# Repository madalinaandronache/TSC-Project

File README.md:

# OpenBook - E-book Reader Open-Source

Student: Andronache Madalina-Georgiana
Grupa: 332CC

Urmatorul fisier contine informatii despre rezolvarea cerintelor
propuse.

Cuprins:

0. Descrierea cerintelor
1. Diagrama bloc
2. BOM - Bill of Materials
3. Functionalitatea hardware
4. Pini utilizați pe ESP32-C6 și justificare
5. Observatii

## 0. Descrierea cerintelor

OpenBook este un e-book reader open-source, conceput să fie ieftin, compact și ușor de produs. 
Acest proiect este realizat în cadrul unui start-up educațional, iar scopul este dezvoltarea unui 
dispozitiv complet funcțional, pornind de la specificațiile sistemului până la fișierele de fabricație.

## 1. Diagrama bloc

## 2. BOM - Bill of Materials

| Device | Value | Check_Price | Datasheet |
|--------|-------|-------------|-----------|
| ADAFRUIT_LEDCHIP-LED0603 | - | [Link](https://www.snapeda.com/parts/KP-1608SURCK/Kingbright/view-part/?ref=search&t=LED%200603) | [Link](https://www.snapeda.com/parts/KP-1608SURCK/Kingbright/datasheet/) |
| SJ | - | [Link](https://grabcad.com/library/solder-jumpers-1) | - |
| EAGLE-LTSPICE_C | 0.1uF/50V | [Link](https://componentsearchengine.com/part-view/CC0402MRX5R5BB106/YAGEO) | [Link](https://componentsearchengine.com/Datasheets/2/CC0402MRX5R5BB106.pdf) |
| ESP32_WROVER_EAGLE-LTSPICE_R | 0.47 | [Link](https://componentsearchengine.com/part-view/R0402%201%25%20100%20K%20(RC0402FR-07100KL)/YAGEO) | [Link](https://www.yageo.com/upload/media/product/products/datasheet/rchip/PYu-RC_Group_51_RoHS_L_12.pdf) |
| ESP32_WROVER_EAGLE-LTSPICE_R | 100K | [Link](https://componentsearchengine.com/part-view/R0402%201%25%20100%20K%20(RC0402FR-07100KL)/YAGEO) | [Link](https://www.yageo.com/upload/media/product/products/datasheet/rchip/PYu-RC_Group_51_RoHS_L_12.pdf) |
| EAGLE-LTSPICE_C | 100nF | [Link](https://componentsearchengine.com/part-view/CC0402MRX5R5BB106/YAGEO) | [Link](https://componentsearchengine.com/Datasheets/2/CC0402MRX5R5BB106.pdf) |
| RCL_CPOL-EUCT3528 | 100uF TANT | [Link](https://www.snapeda.com/parts/TAJB475K025RNJ/AVX/view-part/?ref=dk&t=capacitor%203528&con_ref=None) | [Link](https://s3.amazonaws.com/snapeda/datasheet/TAJB475K025RNJ_AVX.pdf) |
| ESP32_WROVER_EAGLE-LTSPICE_R | 10K | [Link](https://componentsearchengine.com/part-view/R0402%201%25%20100%20K%20(RC0402FR-07100KL)/YAGEO) | [Link](https://www.yageo.com/upload/media/product/products/datasheet/rchip/PYu-RC_Group_51_RoHS_L_12.pdf) |
| EAGLE-LTSPICE_C | 10uF | [Link](https://componentsearchengine.com/part-view/CC0402MRX5R5BB106/YAGEO) | [Link](https://componentsearchengine.com/Datasheets/2/CC0402MRX5R5BB106.pdf) |
| 112A-TAAR-R03_ATTEND | 112A-TAAR-R03_ATTEND | [Link](https://store.comet.srl.ro/Catalogue/Product/43497/) | [Link](https://store.comet.bg/download-file.php?id=8824) |
| ESP32_WROVER_EAGLE-LTSPICE_R | 15 | [Link](https://componentsearchengine.com/part-view/R0402%201%25%20100%20K%20(RC0402FR-07100KL)/YAGEO) | [Link](https://www.yageo.com/upload/media/product/products/datasheet/rchip/PYu-RC_Group_51_RoHS_L_12.pdf) |
| EAGLE-LTSPICE_C | 1uF | [Link](https://componentsearchengine.com/part-view/CC0402MRX5R5BB106/YAGEO) | [Link](https://componentsearchengine.com/Datasheets/2/CC0402MRX5R5BB106.pdf) |
| EAGLE-LTSPICE_C | 1uF/50V | [Link](https://componentsearchengine.com/part-view/CC0402MRX5R5BB106/YAGEO) | [Link](https://componentsearchengine.com/Datasheets/2/CC0402MRX5R5BB106.pdf) |
| ESP32_WROVER_EAGLE-LTSPICE_R | 2.2 | [Link](https://componentsearchengine.com/part-view/R0402%201%25%20100%20K%20(RC0402FR-07100KL)/YAGEO) | [Link](https://www.yageo.com/upload/media/product/products/datasheet/rchip/PYu-RC_Group_51_RoHS_L_12.pdf) |
| ESP32_WROVER_EAGLE-LTSPICE_R | 200 | [Link](https://componentsearchengine.com/part-view/R0402%201%25%20100%20K%20(RC0402FR-07100KL)/YAGEO) | [Link](https://www.yageo.com/upload/media/product/products/datasheet/rchip/PYu-RC_Group_51_RoHS_L_12.pdf) |
| ESP32_WROVER_SPARKFUN-DISCRETESEMI_MOSFET_PCH-DMG2305UX-7 | 20V/4.2A/52m?/1.4W | [Link](https://componentsearchengine.com/part-view/DMG2305UX-7/Diodes%20Incorporated) | [Link](https://www.diodes.com//assets/Datasheets/DMG2305UX.pdf) |
| ESP32_WROVER_EAGLE-LTSPICE_R | 2K | [Link](https://componentsearchengine.com/part-view/R0402%201%25%20100%20K%20(RC0402FR-07100KL)/YAGEO) | [Link](https://www.yageo.com/upload/media/product/products/datasheet/rchip/PYu-RC_Group_51_RoHS_L_12.pdf) |
| EAGLE-LTSPICE_C | 4.7uF | [Link](https://componentsearchengine.com/part-view/CC0402MRX5R5BB106/YAGEO) | [Link](https://componentsearchengine.com/Datasheets/2/CC0402MRX5R5BB106.pdf) |
| EAGLE-LTSPICE_C | 4.7uF/25V | [Link](https://componentsearchengine.com/part-view/CC0402MRX5R5BB106/YAGEO) | [Link](https://componentsearchengine.com/Datasheets/2/CC0402MRX5R5BB106.pdf) |
| ESP32_WROVER_EAGLE-LTSPICE_R | 5k1 | [Link](https://componentsearchengine.com/part-view/R0402%201%25%20100%20K%20(RC0402FR-07100KL)/YAGEO) | [Link](https://www.yageo.com/upload/media/product/products/datasheet/rchip/PYu-RC_Group_51_RoHS_L_12.pdf) |
| 744043680IND_4828-WE-TPC_WRE | 68uH | [Link](https://ro.mouser.com/ProductDetail/Wurth-Elektronik/744043680?qs=PGXP4M47uW6VkZq%252BkzjrHA%3D%3D&_gl=1*5xajdn*_ga*MzY2ODgyMjE4LjE3NDM2NzQxODk.*_ga_15W4STQT4T*MTc0Mzg3MzkxMy40LjAuMTc0Mzg3MzkxNi41Ny4wLjA.) | [Link](https://www.we-online.com/components/products/datasheet/744043680.pdf) |
| BD5229G-TR | BD5229G-TR | [Link](https://componentsearchengine.com/part-view/BD5229G-TR/ROHM%20Semiconductor) | [Link](https://datasheet.datasheetarchive.com/originals/distributors/Datasheets_SAMA/f2b9741ef86007909f138d561a359946.pdf) |
| ESP32_WROVER_BME680_BME680 | BME688 | [Link](https://www.snapeda.com/parts/BME680/Bosch/view-part/?welcome=home) | [Link](https://www.snapeda.com/parts/BME680/Bosch%20Sensortec/datasheet/) |
| BUTTON_CUSYOMV1V2 | BUTTON_CUSYOMV1V2 | [Link](https://industry.panasonic.com/global/en/products/control/switch/light-touch/number/evqpuj02k) | [Link](https://industry.panasonic.com/global/en/downloads?tab=catalog&small_g_cd=203&part_no=EVQPUJ02K) |
| CPH3225A | CPH3225A | [Link](https://www.snapeda.com/parts/CPH3225A/Seiko+Instruments/view-part/?ref=eda) | [Link](https://www.snapeda.com/parts/CPH3225A/Seiko+Instruments/view-part/?ref=eda ) |
| DS3231SN# | DS3231SN# | [Link](https://www.snapeda.com/parts/DS3231SN%23/Analog+Devices/view-part/?ref=eda) | [Link](https://www.snapeda.com/parts/DS3231SN%23/Analog+Devices/view-part/?ref=eda) |
| ESP32-C6-WROOM-1-N8 | ESP32-C6-WROOM-1-N8 | [Link](https://www.snapeda.com/parts/ESP32-C6-WROOM-1-N8/Espressif+Systems/view-part/?ref=eda) | [Link](https://www.snapeda.com/parts/ESP32-C6-WROOM-1-N8/Espressif+Systems/view-part/?ref=eda) |
| ESP32C6_VARISTORCN1812 | ESP32C6_VARISTORCN1812 | [Link](https://www.mouser.co.uk/ProductDetail/EPCOS-TDK/B72520T0350K062?qs=dEfas%2FXlABIszF52uu7vrg%3D%3D) | [Link](https://www.tdk-electronics.tdk.com/inf/75/db/CTVS_14/Surge_protection_series.pdf) |
| ESP32_WROVER_SPARKFUN-IC-POWER_MCP73831 | ESP32_WROVER_SPARKFUN-IC-POWER_MCP73831 | [Link](https://ro.mouser.com/ProductDetail/Microchip-Technology/MCP73831T-2ACI-OT?qs=yUQqVecv4qvbBQBGbHx0Mw%3D%3D) | [Link](https://ro.mouser.com/datasheet/2/268/MCP73831_Family_Data_Sheet_DS20001984H-3441711.pdf) |
| FH34SRJ-24S-0.5SH_99_ | FH34SRJ-24S-0.5SH_99_ | [Link](https://componentsearchengine.com/part-view/FH34SRJ-24S-0.5SH(99)/Hirose) | [Link](https://www.hirose.com/en/product/document?clcode=CL0580-1255-6-99&productname=FH34SRJ-24S-0.5SH(99)&series=FH34SRJ&documenttype=2DDrawing&lang=en&documentid=0000990903) |
| MAX17048G+T10 | MAX17048G+T10 | [Link](https://www.snapeda.com/parts/MAX17048G+T10/Analog+Devices/view-part/?ref=eda) | [Link](https://www.snapeda.com/parts/MAX17048G+T10/Analog+Devices/view-part/?ref=eda) |
| MBR0530. | MBR0530. | [Link](https://www.snapeda.com/parts/MBR0530/Onsemi/view-part/?ref=eda) | [Link](https://www.snapeda.com/parts/MBR0530/ON%20Semiconductor/datasheet/) |
| PGB1010603MR. | PGB1010603MR. | [Link](https://www.snapeda.com/parts/PGB1010603MR/Littelfuse/view-part/?ref=eda) | [Link](https://www.snapeda.com/parts/PGB1010603MR/Littelfuse%20Inc./datasheet/) |
| QWIIC_CONNECTORJS-1MM | QWIIC_RIGHT_ANGLE | [Link](https://www.digikey.lt/en/models/926710 ) | [Link](https://www.digikey.lt/en/models/926710) |
| SAMACSYS_PARTS_USB4110-GF-A | SAMACSYS_PARTS_USB4110-GF-A | [Link](https://componentsearchengine.com/part-view/USB4110-GF-A/GCT%20(GLOBAL%20CONNECTOR%20TECHNOLOGY)) | [Link](https://gct.co/files/drawings/usb4110.pdf) |
| ESP32_WROVER_AVX---SD0805S020S1R0_AVX_SD0805S020S1R0_0_0AVX_SD0805S020S1R0_0_0 | SD0805S020S1R0 | [Link](https://ro.mouser.com/ProductDetail/KYOCERA-AVX/SD0805S020S1R0?qs=jCA%252BPfw4LHbpkAoSnwrdjw%3D%3D) | [Link](http://datasheets.avx.com/schottky.pdf) |
| SI1308EDL-T1-GE3 | SI1308EDL-T1-GE3 | [Link](https://www.snapeda.com/parts/SI1308EDL-T1-GE3/Vishay+Siliconix/view-part/?ref=eda) | [Link](https://www.snapeda.com/parts/SI1308EDL-T1-GE3/Vishay+Siliconix/view-part/?ref=eda) |
| TPV1 | TPV1 | Custom made | - |
| USBLC6-2SC6Y | USBLC6-2SC6Y | [Link](https://www.snapeda.com/parts/USBLC6-2SC6Y/STMicroelectronics/view-part/?ref=eda) | [Link](https://www.snapeda.com/parts/USBLC6-2SC6Y/STMicroelectronics/view-part/?ref=eda) |
| W25Q512JVEIQ | W25Q512JVEIQ | [Link](https://www.snapeda.com/parts/W25Q512JVEIQ/Winbond+Electronics/view-part/?ref=eda) | [Link](https://www.snapeda.com/parts/W25Q512JVEIQ/Winbond+Electronics/view-part/?ref=eda) |
| XC6220A331MR-G | XC6220A331MR-G | [Link](https://componentsearchengine.com/part-view/XC6220A331MR-G/Torex) | [Link](https://product.torexsemi.com/system/files/series/xc6220.pdf) |

## 3. Functionalitatea hardware

Prezentam in detaliu functionalitatea hardware a device-ului:

| Nr. | Componentă                              |
|-----|------------------------------------------|
| 1   | Microcontroller – ESP32-C6-WROOM-1       |
| 2   | Afișaj E-Ink – Waveshare WSH-13187, 7.5” |
| 3   | Senzor Mediu – Bosch BME688              |
| 4   | Baterie și Management Energie            |
| 5   | Butoane – 3x Tactile Switch              |
| 6   | Port USB-C                               |
| 7   | Conector Qwiic / STEMMA QT (I²C)         |
| 8   | Slot MicroSD – Attend 112A-TAAR-R03      |
| 9   | RTC – DS3231                             |

### 3.1. Microcontroller – ESP32-C6-WROOM-1
- **Procesor:** 32-bit RISC-V @ 160MHz
- **Memorie:** 512KB SRAM + 8MB flash extern (W25Q512JVEIQ)
- **Conectivitate:** Wi-Fi 6 (802.11ax), Bluetooth 5 LE, USB 2.0 Full-Speed
- **Periferice:** SPI, I²C, UART, GPIO multiple
- **Consum:** <50µA în deep sleep, moduri low-power disponibile
- **Securitate:** Secure boot, criptare flash, criptografie hardware

### 3.2. Afișaj E-Ink – Waveshare WSH-13187, 7.5”
- **Rezoluție:** 800x480, monocrom
- **Interfață:** SPI (4-wire) + CS, DC, RST, BUSY
- **Consum:** 15–25mA în timpul refresh-ului, zero static
- **Motivație:** Consum aproape zero în mod static, ideal pentru e-readere

### 3.3. Senzor Mediu – Bosch BME688
- **Parametri:** Temperatură, Umiditate, Presiune, Calitate Aer (eCO2, TVOC)
- **Precizie:** ±1°C, ±3%, ±1 hPa
- **Interfață:** I²C (400kHz)
- **Consum:** 2.1µA standby, 3.6mA peak
- **Motivație:** Multi-senzor compact, ideal pentru feedback ambiental

### 3.4. Baterie și Management Energie
- **Tip:** Li-Po 3.7V, 2500mAh
- **Fuel Gauge:** MAX17048 (I²C)
- **Charging IC:** MCP73831 – încărcare 5V/1A prin USB-C
- **LDO:** 3.3V stabil pentru întreaga placă
- **Consum Total:**  
  - Activ: 100–150mA  
  - Deep Sleep: <50µA

### 3.5. Butoane – 3x Tactile Switch
- **Model:** Panasonic EVQ-Q2A03W
- **Conectare:** GPIO + debounce hardware (RC)
- **Funcții:** Navigare meniu, pagină înainte/înapoi, confirmare

### 3.6. Port USB-C
- **Rol:** Încărcare + transfer date (USB 2.0)
- **Protecții:** ESD + terminare corectă
- **Capabilități:** OTA updates prin Wi-Fi / firmware update prin USB

### 3.7. Conector Qwiic / STEMMA QT (I²C)
- **Pini:** VCC, GND, SDA, SCL
- **Utilitate:** Extensibilitate rapidă prin senzori/modul I²C

### 3.8. Slot MicroSD – Attend 112A-TAAR-R03
- **Funcție:** Stocare externă (ebooks, logs, firmware)
- **Interfață:** SPI

### 3.9. RTC – DS3231
- **Precizie:** ±2ppm
- **Interfață:** I²C
- **Backup:** Supercapacitor

---

### Comunicații & Interfețe

| Tip       | Componente                                          |
|-----------|-----------------------------------------------------|
| **SPI**   | E-Paper, Flash extern, SD Card (în mod SPI)         |
| **I²C**   | BME688, MAX17048, DS3231, Qwiic/Stemma              |
| **USB**   | Încărcare și transfer date prin USB-C               |
| **GPIO**  | Butoane, semnale control afișaj, charging enable    |

---

### Consum de Energie (Estimativ)

| Modul             | Consum Tipic       |
|------------------|--------------------|
| ESP32-C6 activ    | 80–100mA           |
| E-Paper refresh   | 15–25mA            |
| BME688 activ      | 3.6mA              |
| MAX17048          | ~50µA              |
| DS3231 (RTC)      | 3.5mA / 1µA backup |
| Deep Sleep Total  | <50–100µA          |

---

### Dimensiuni & Alte Detalii
- **Dimensiuni:** 175 x 114 x 10 mm
- **Greutate:** 250g
- **Material carcasă:** ABS sau policarbonat, design ergonomic
- **Display:** Montat cu decupaj integrat
- **Producție:** PCB 2-layer, ENIG, carcasă prin injecție

---

## 4. Pini utilizați pe ESP32-C6 și justificare

| Pin ESP32-C6 | Componentă / Semnal                | De ce?                                                                 |
|--------------|-------------------------------------|------------------------------------------------------------------------|
| GPIO1        | I²C SDA (BME688, MAX17048, DS3231, Qwiic) | Linie partajată I²C – economisește pini și permite extinderea facilă |
| GPIO2        | I²C SCL (BME688, MAX17048, DS3231, Qwiic) | Clock I²C pentru toți senzorii și extensii Qwiic                     |
| GPIO5        | SPI MISO (E-Paper, Flash extern)    | Linie comună de intrare date în SPI                                   |
| GPIO6        | SPI MOSI (E-Paper, Flash extern)    | Linie de ieșire date către e-paper și flash                           |
| GPIO7        | SPI CLK                             | Semnal de clock pentru magistrala SPI                                 |
| GPIO8        | E-Paper CS                          | Selectează afișajul pe magistrala SPI                                 |
| GPIO9        | E-Paper DC (Data/Command)           | Comută între comandă și date către e-paper                            |
| GPIO10       | E-Paper RST                         | Reset hardware e-paper                                                |
| GPIO11       | E-Paper BUSY                        | Pin de stare (ocupat/liber) de la display                             |
| GPIO12       | Button #1                           | Intrare digitală pentru navigare pagină înainte                      |
| GPIO13       | Button #2                           | Intrare digitală pentru navigare pagină înapoi                       |
| GPIO14       | Button #3                           | Intrare digitală pentru selectare/opțiune                            |
| GPIO15       | MAX17048 ALERT (opțional)           | Pin de alertă nivel scăzut baterie                                    |
| GPIO16       | USB D+ (intern la USB PHY)          | Linie USB 2.0 (fixă pe ESP32-C6)                                      |
| GPIO17       | USB D- (intern la USB PHY)          | Linie USB 2.0 (fixă pe ESP32-C6)                                      |
| GPIO18       | LED Status (opțional)               | Indicator pentru activitate Wi-Fi, charging, notificări               |
| GPIO19       | SD Card CS                          | Selectare chip pentru card microSD (SPI)                              |
| GPIO20       | SD Card MISO                        | Citire date de pe card microSD                                        |
| GPIO21       | SD Card MOSI                        | Scriere date pe card microSD                                          |
| GPIO4        | SD Card CLK                         | Semnal de clock pentru card microSD (SPI)                             |

## 5. Observatii

Fun to make, dar mult prea solicitant. Realizat in aproximativ 60 h.

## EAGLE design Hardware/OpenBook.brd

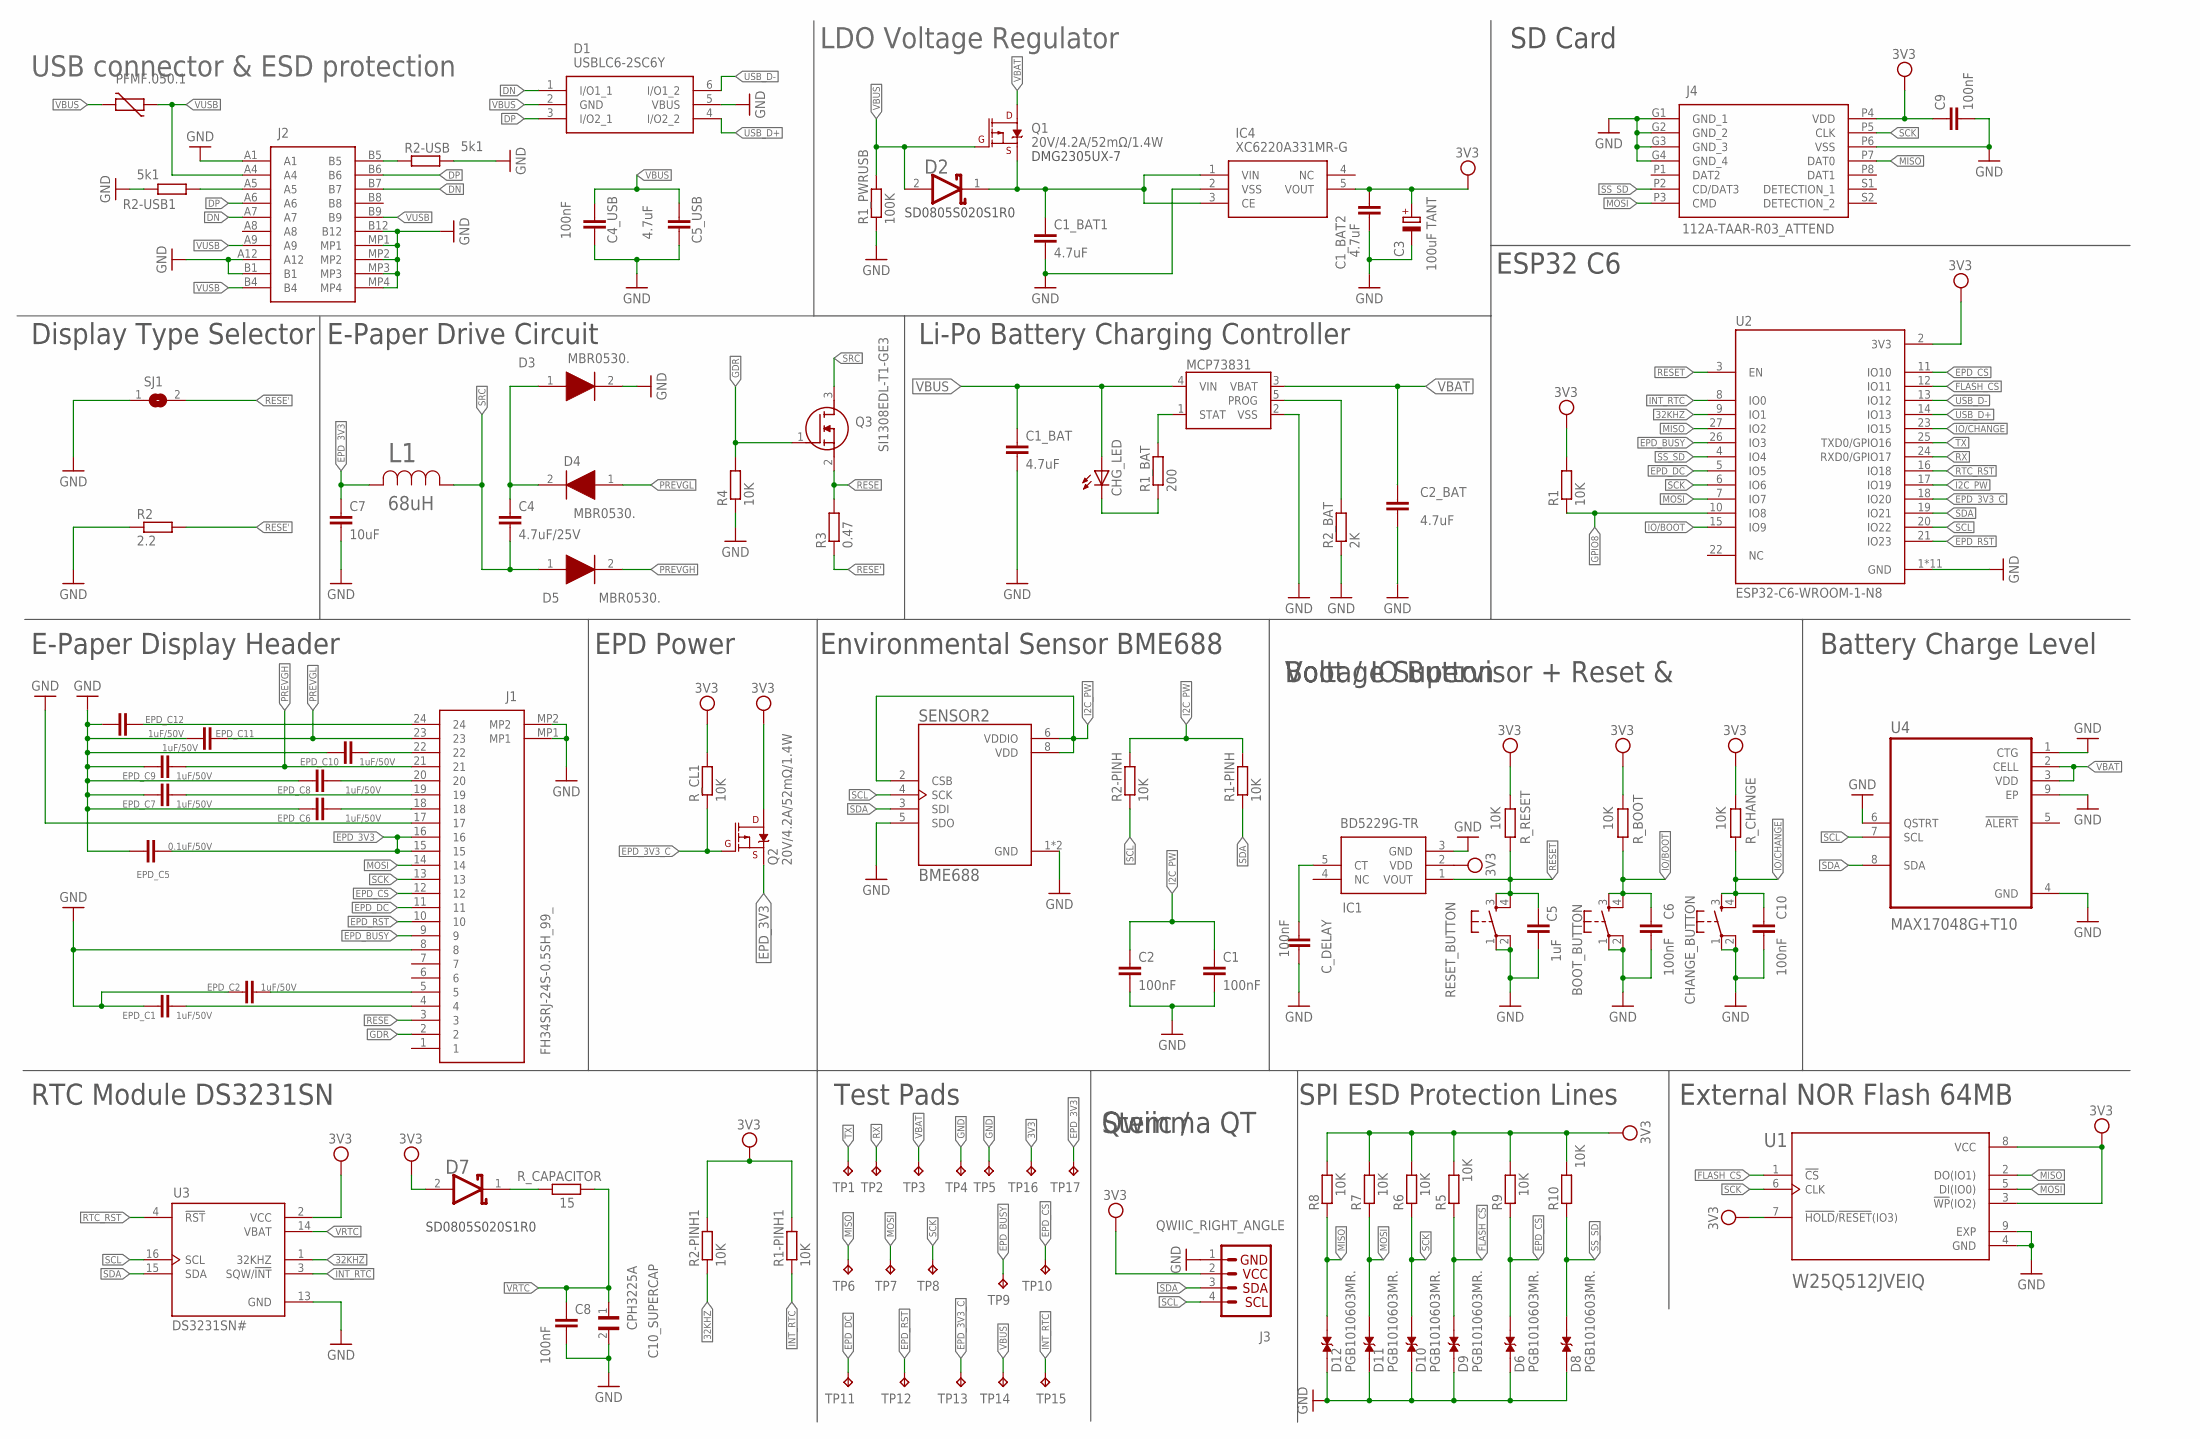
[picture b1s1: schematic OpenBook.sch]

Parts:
BOOT_BUTTON: BUTTON_CUSYOMV1V2; MYBUTTON
C1, C2, C4_USB, C6, C8, C9, C10: 100nF; EAGLE-LTSPICE_C0402
C1_BAT, C1_BAT1, C1_BAT2, C2_BAT, C5_USB: 4.7uF; EAGLE-LTSPICE_C0402
C3: 100uF TANT; RCL_CT3528
C4: 4.7uF/25V; EAGLE-LTSPICE_C0402
C5: 1uF; EAGLE-LTSPICE_C0402
C7: 10uF; EAGLE-LTSPICE_C0402
C10_SUPERCAP: CPH3225A; CAPCP3225X100N
CHANGE_BUTTON: BUTTON_CUSYOMV1V2; MYBUTTON
CHG_LED: ADAFRUIT_LEDCHIP-LED0603; ADAFRUIT_CHIP-LED0603
C_DELAY: 100nF; EAGLE-LTSPICE_C0402
D1: USBLC6-2SC6Y; SOT95P280X145-6N
D2, D7: SD0805S020S1R0; ESP32_WROVER_AVX---SD0805S020S1R0_AVX_SD0805S020S1R0_0
D3, D4, D5: MBR0530.; SOD3716X135N
D6, D8, D9, D10, D11, D12: PGB1010603MR.; DIOC1608X36N
EPD_C1, EPD_C2, EPD_C6, EPD_C7, EPD_C8, EPD_C9, EPD_C10, EPD_C11, EPD_C12: 1uF/50V; EAGLE-LTSPICE_C0402
EPD_C5: 0.1uF/50V; EAGLE-LTSPICE_C0402
IC1: BD5229G-TR; SOT95P280X125-5N
IC4: XC6220A331MR-G; SOT95P280X120-5N
J1: FH34SRJ-24S-0.5SH_99_; FH34SRJ24S05SH99
J2: SAMACSYS_PARTS_USB4110-GF-A; SAMACSYS_PARTS_USB4110GFA
J3: QWIIC_RIGHT_ANGLE; JST04_1MM_RA
J4: 112A-TAAR-R03_ATTEND; 112ATAARR03ATTEND
L1: 68uH; IND_4828-WE-TPC_WRE
MCP73831: ESP32_WROVER_SPARKFUN-IC-POWER_MCP73831; ESP32_WROVER_SPARKFUN-IC-POWER_SOT23-5
PFMF.050.1: ESP32C6_VARISTORCN1812; ESP32C6_VARISTOR_CT/CN1812
Q1, Q2: 20V/4.2A/52mΩ/1.4W; ESP32_WROVER_SPARKFUN-DISCRETESEMI_SOT23-3
Q3: SI1308EDL-T1-GE3; SOT65P210X110-3N
R1, R1-PINH, R1-PINH1, R2-PINH, R2-PINH1, R4, R5, R6, R7, R8, R9, R10: 10K; ESP32_WROVER_EAGLE-LTSPICE_R0402
R1_BAT: 200; ESP32_WROVER_EAGLE-LTSPICE_R0402
R1_PWRUSB: 100K; ESP32_WROVER_EAGLE-LTSPICE_R0402
R2: 2.2; ESP32_WROVER_EAGLE-LTSPICE_R0402
R2-USB, R2-USB1: 5k1; ESP32_WROVER_EAGLE-LTSPICE_R0402
R2_BAT: 2K; ESP32_WROVER_EAGLE-LTSPICE_R0402
R3: 0.47; ESP32_WROVER_EAGLE-LTSPICE_R0402
RESET_BUTTON: BUTTON_CUSYOMV1V2; MYBUTTON
R_BOOT: 10K; ESP32_WROVER_EAGLE-LTSPICE_R0402
R_CAPACITOR: 15; ESP32_WROVER_EAGLE-LTSPICE_R0402
R_CHANGE: 10K; ESP32_WROVER_EAGLE-LTSPICE_R0402
R_CL1: 10K; ESP32_WROVER_EAGLE-LTSPICE_R0402
R_RESET: 10K; ESP32_WROVER_EAGLE-LTSPICE_R0402
SENSOR2: BME688; ESP32_WROVER_BME680_PSON80P300X300X100-8N
SJ1: SJ
TP1, TP2, TP3, TP4, TP5, TP6, TP7, TP8, TP9, TP10, TP11, TP12, TP13, TP14, TP15, TP16, TP17: TPV1; TP20R
U1: W25Q512JVEIQ; SON127P600X800X80-9N
U2: ESP32-C6-WROOM-1-N8; XCVR_ESP32-C6-WROOM-1-N8
U3: DS3231SN#; SOIC127P1032X265-16N
U4: MAX17048G+T10; SON50P200X200X80-9N

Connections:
3V3: C1_BAT2.1, C3.+, C9.1, D7.2 (ANODE), IC1.2 (VDD), IC4.5 (VOUT), J3.2, J4.P4 (VDD), Q2.3 (D), R1.2, R1-PINH1.2, R2-PINH1.2, R5.2, R6.2, R7.2, R8.2, R9.2, R10.2, R_BOOT.2, R_CHANGE.2, R_CL1.2, R_RESET.2, TP16.TP, U1.3 (!WP!(IO2)), U1.7 (!HOLD!/!RESET!(IO3)), U1.8 (VCC), U2.2 (3V3), U3.2 (VCC)
32KHZ: R2-PINH1.1, U2.9 (IO1), U3.1 (32KHZ)
DN: D1.1 (I/O1_1), J2.A7, J2.B7
DP: D1.3 (I/O2_1), J2.A6, J2.B6
EPD_3V3: C7.1, EPD_C5.2, J1.15, J1.16, L1.2, Q2.2 (S), TP17.TP
EPD_3V3_C: Q2.1 (G), R_CL1.1, TP13.TP, U2.18 (IO20)
EPD_BUSY: J1.9, TP9.TP, U2.26 (IO3)
EPD_CS: D6.2, J1.12, R9.1, TP10.TP, U2.11 (IO10)
EPD_DC: J1.11, TP11.TP, U2.5 (IO5)
EPD_RST: J1.10, TP12.TP, U2.21 (IO23)
FLASH_CS: D9.2, R5.1, U1.1 (!CS), U2.12 (IO11)
GDR: J1.2, Q3.1 (G), R4.2
GND: BOOT_BUTTON.1, BOOT_BUTTON.2, C1.2, C1_BAT.2, C1_BAT1.2, C1_BAT2.2, C2.2, C2_BAT.2, C3.-, C4_USB.2, C5.2, C5_USB.2, C6.2, C7.2, C8.2, C9.2, C10.2, C10_SUPERCAP.2, CHANGE_BUTTON.1, CHANGE_BUTTON.2, C_DELAY.2, D1.5 (VBUS), D3.2 (K), D6.1, D8.1, D9.1, D10.1, D11.1, D12.1, EPD_C1.1, EPD_C2.1, EPD_C5.1, EPD_C6.1, EPD_C7.1, EPD_C8.1, EPD_C9.1, EPD_C10.1, EPD_C11.1, EPD_C12.1, IC1.3 (GND), IC4.2 (VSS), J1.8, J1.17, J1.MP1, J1.MP2, J2.A1, J2.A12, J2.B1, J2.B12, J2.MP1, J2.MP2, J2.MP3, J2.MP4, J3.1, J4.G1 (GND_1), J4.G2 (GND_2), J4.G3 (GND_3), J4.G4 (GND_4), J4.P6 (VSS), MCP73831.2 (VSS), R1_PWRUSB.1, R2.1, R2-USB.2, R2-USB1.1, R2_BAT.1, R4.1, RESET_BUTTON.1, RESET_BUTTON.2, SENSOR2.1 (GND), SENSOR2.5 (SDO), SENSOR2.7 (GND), SJ1.1, TP4.TP, TP5.TP, U1.4 (GND), U1.9 (EXP), U2.1 (GND), U2.28 (GND), U2.29_1 (GND), U2.29_2 (GND), U2.29_3 (GND), U2.29_4 (GND), U2.29_5 (GND), U2.29_6 (GND), U2.29_7 (GND), U2.29_8 (GND), U2.29_9 (GND), U3.13 (GND), U4.1 (CTG), U4.4 (GND), U4.6 (QSTRT), U4.9 (EP)
GPIO8: R1.1, U2.10 (IO8)
I2C_PW: C1.1, C2.1, R1-PINH.2, R2-PINH.2, SENSOR2.2 (CSB), SENSOR2.6 (VDDIO), SENSOR2.8 (VDD), U2.17 (IO19)
INT_RTC: R1-PINH1.1, TP15.TP, U2.8 (IO0), U3.3 (SQW/!INT)
IO/BOOT: BOOT_BUTTON.3, BOOT_BUTTON.4, C6.1, R_BOOT.1, U2.15 (IO9)
IO/CHANGE: C10.1, CHANGE_BUTTON.3, CHANGE_BUTTON.4, R_CHANGE.1, U2.23 (IO15)
MISO: D12.2, J4.P7 (DAT0), R8.1, TP6.TP, U1.2 (DO(IO1)), U2.27 (IO2)
MOSI: D11.2, J1.14, J4.P3 (CMD), R7.1, TP7.TP, U1.5 (DI(IO0)), U2.7 (IO7)
unnamed: D7.1 (CATHODE), R_CAPACITOR.1
unnamed: J2.A5, R2-USB1.2
unnamed: J2.B5, R2-USB.1
unnamed: C4.1, D3.1 (A), D4.2 (K)
unnamed: C1_BAT1.1, D2.1 (CATHODE), IC4.1 (VIN), IC4.3 (CE), Q1.2 (S)
unnamed: MCP73831.1 (STAT), R1_BAT.2
unnamed: MCP73831.5 (PROG), R2_BAT.2
unnamed: C_DELAY.1, IC1.5 (CT)
unnamed: CHG_LED.C, R1_BAT.1
unnamed: EPD_C1.2, J1.4
unnamed: EPD_C2.2, J1.5
unnamed: EPD_C6.2, J1.18
unnamed: EPD_C7.2, J1.19
unnamed: EPD_C10.2, J1.22
unnamed: EPD_C8.2, J1.20
unnamed: EPD_C12.2, J1.24
PREVGH: D5.2 (K), EPD_C9.2, J1.21
PREVGL: D4.1 (A), EPD_C11.2, J1.23
RESE: J1.3, Q3.2 (S), R3.2
RESE': R2.2, R3.1, SJ1.2
RESET: C5.1, IC1.1 (VOUT), RESET_BUTTON.3, RESET_BUTTON.4, R_RESET.1, U2.3 (EN)
RTC_RST: U2.16 (IO18), U3.4 (!RST)
RX: TP2.TP, U2.24 (RXD0/GPIO17)
SCK: D10.2, J1.13, J4.P5 (CLK), R6.1, TP8.TP, U1.6 (CLK), U2.6 (IO6)
SCL: J3.4, R2-PINH.1, SENSOR2.4 (SCK), U2.20 (IO22), U3.16 (SCL), U4.7 (SCL)
SDA: J3.3, R1-PINH.1, SENSOR2.3 (SDI), U2.19 (IO21), U3.15 (SDA), U4.8 (SDA)
SRC: C4.2, D5.1 (A), L1.1, Q3.3 (D)
SS_SD: D8.2, J4.P2 (CD/DAT3), R10.1, U2.4 (IO4)
TX: TP1.TP, U2.25 (TXD0/GPIO16)
USB_D+: D1.4 (I/O2_2), U2.14 (IO13)
USB_D-: D1.6 (I/O1_2), U2.13 (IO12)
VBAT: C2_BAT.1, MCP73831.3 (VBAT), Q1.3 (D), TP3.TP, U4.2 (CELL), U4.3 (VDD)
VBUS: C1_BAT.1, C4_USB.1, C5_USB.1, CHG_LED.A, D1.2 (GND), D2.2 (ANODE), MCP73831.4 (VIN), PFMF.050.1.2, Q1.1 (G), R1_PWRUSB.2, TP14.TP
VRTC: C8.1, C10_SUPERCAP.1, R_CAPACITOR.2, U3.14 (VBAT)
VUSB: J2.A4, J2.A9, J2.B4, J2.B9, PFMF.050.1.1

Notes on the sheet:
USB connector & ESD protection
LDO Voltage Regulator
SD Card
Display Type Selector
E-Paper Drive Circuit
Li-Po Battery Charging Controller
ESP32 C6
E-Paper Display Header
EPD Power
Environmental Sensor BME688
Voltage Supervisor + Reset &
Boot / IO Button
Battery Charge Level
RTC Module DS3231SN
Test Pads
Qwiic /
Stemma QT
SPI ESD Protection Lines
External NOR Flash 64MB
SD0805S020S1R0
DMG2305UX-7

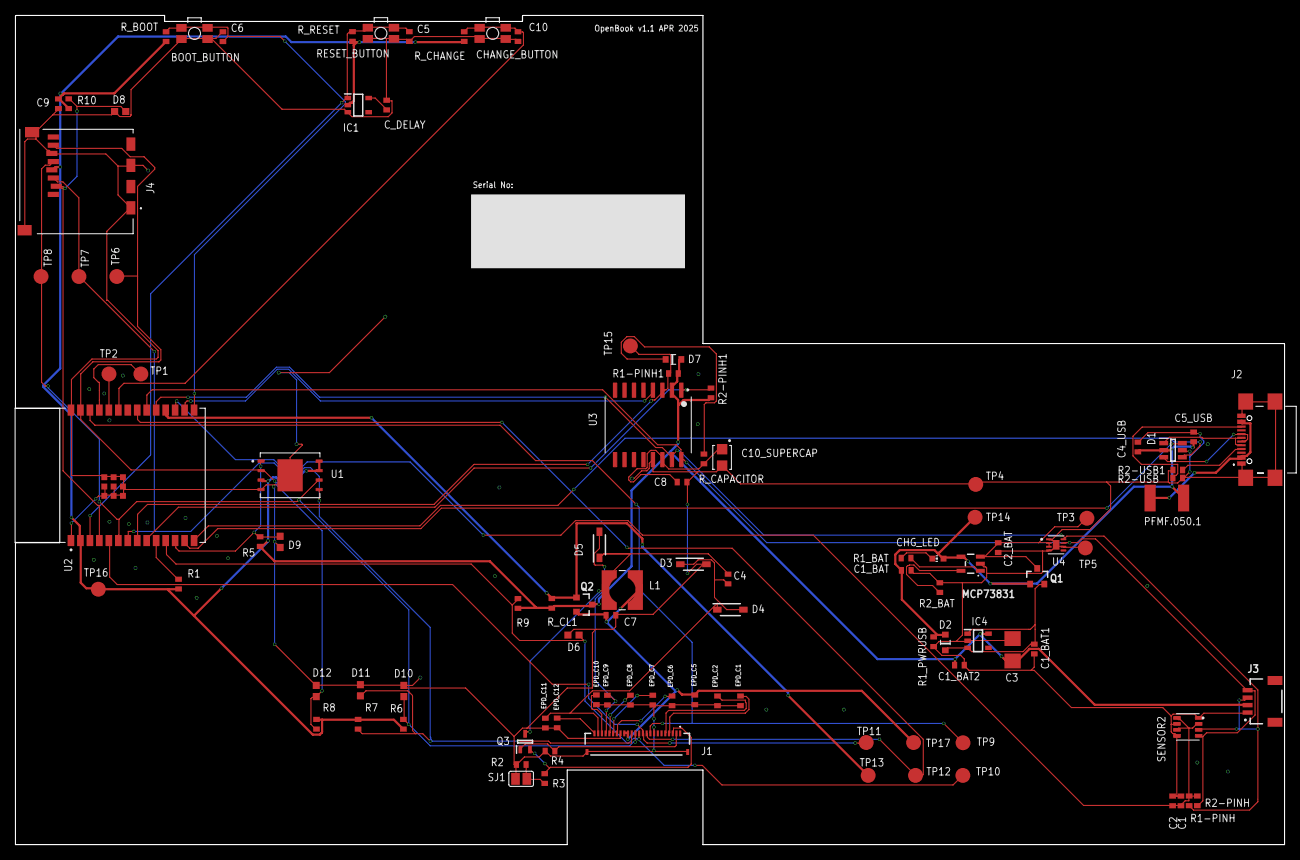
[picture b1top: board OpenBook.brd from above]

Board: 2 copper layers, 170.2 x 111.2 mm, 103 parts (0 on the bottom side), 55 nets.

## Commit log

2025-04-05 Create LICENSE
2025-04-05 Added BOM and PnP Files
2025-04-05 Added the gerbers files
2025-04-06 Added the Hardware Parts
2025-04-06 Updated the gerbers zip
2025-04-06 Added some renders of the board
2025-04-06 Added renders with the device
2025-04-06 Added an exploded video
2025-04-06 Added the mechanical files
2025-04-06 Added views for PCB
2025-04-06 Updated gerbers
2025-04-11 Updated 3D part
2025-04-11 Updated the schematic
2025-04-11 Polygon pour updated

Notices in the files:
parts and their libraries:
COPYRIGHT: Copyright (C) 2024 Ultra Librarian. All rights reserved.
